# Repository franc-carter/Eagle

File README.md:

# Eagle
Random Collection of my Eagle Design Files

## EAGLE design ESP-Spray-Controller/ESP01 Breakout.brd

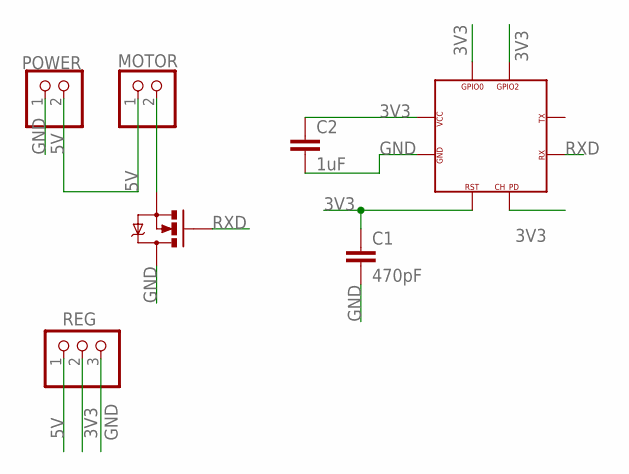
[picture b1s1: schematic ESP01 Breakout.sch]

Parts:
C1: 470pF; CAP-PTH-SMALLEZ
C2: 1uF; CAP-PTH-SMALLEZ
MOTOR: PINHD-1X2/90; 1X02/90
POWER: PINHD-1X2/90; 1X02/90
Q1: MOSFET-NCHANNEL2N7000; TO-92
REG: PINHD-1X3; 1X03
U$2: ESP-01

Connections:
3V3: C1.1, C2.1, REG.2, U$2.CH_PD (CP_PD), U$2.GPIO0, U$2.GPIO2, U$2.RST, U$2.VCC
5V: MOTOR.1, POWER.2, REG.1
GND: C1.2, C2.2, POWER.1, Q1.3 (D), REG.3, U$2.GND
unnamed: MOTOR.2, Q1.1 (S)
RXD: Q1.2 (G), U$2.RXD (RX)

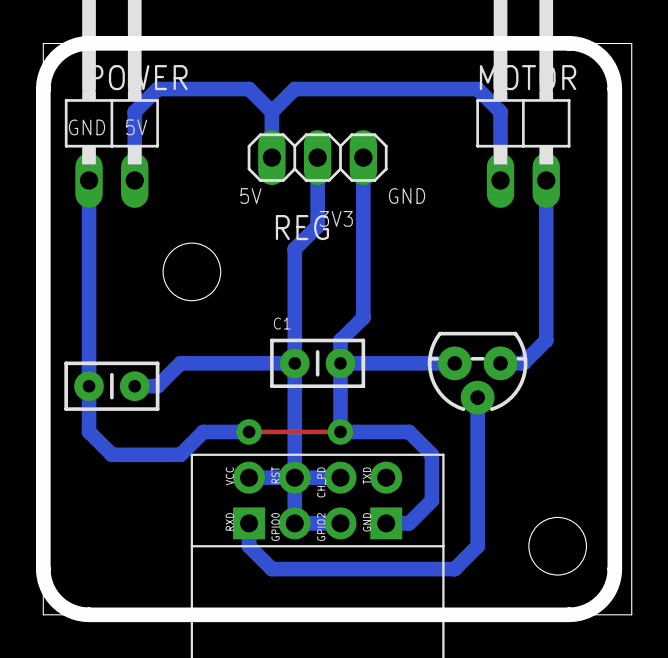
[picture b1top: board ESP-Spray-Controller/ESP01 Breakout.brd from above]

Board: 2 copper layers, 32.3 x 31.7 mm, 7 parts (0 on the bottom side), 5 nets.

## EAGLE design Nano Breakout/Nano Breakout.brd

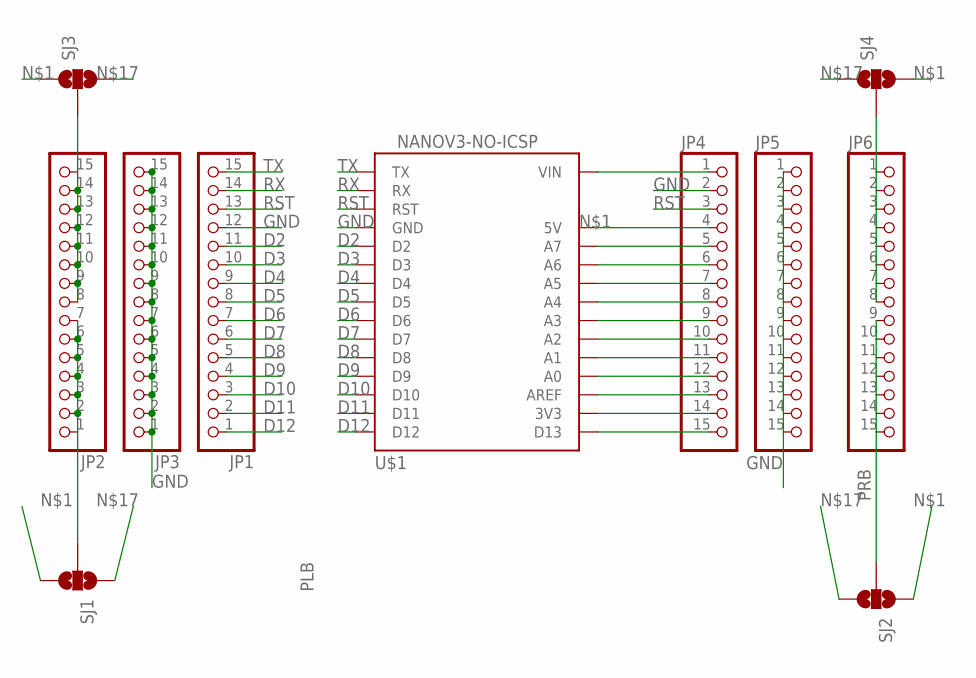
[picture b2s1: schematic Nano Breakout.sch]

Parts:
JP1, JP2, JP3, JP4, JP5, JP6: PINHD-1X15; 1X15
SJ1, SJ2, SJ3, SJ4: JUMPER-PAD-3-NOFULL_BOX_SILK; PAD-JUMPER-3-NO_YES_SILK_FULL_BOX
U$1: NANOV3-NO-ICSP

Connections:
D2: JP1.11, U$1.D2
D3: JP1.10, U$1.D3
D4: JP1.9, U$1.D4
D5: JP1.8, U$1.D5
D6: JP1.7, U$1.D6
D7: JP1.6, U$1.D7
D8: JP1.5, U$1.D8
D9: JP1.4, U$1.D9
D10: JP1.3, U$1.D10
D11: JP1.2, U$1.D11
D12: JP1.1, U$1.D12
GND: JP1.12, JP3.1, JP3.2, JP3.3, JP3.4, JP3.5, JP3.6, JP3.7, JP3.8, JP3.9, JP3.10, JP3.11, JP3.12, JP3.13, JP3.14, JP3.15, JP4.2, JP5.1, JP5.2, JP5.3, JP5.4, JP5.5, JP5.6, JP5.7, JP5.8, JP5.9, JP5.10, JP5.11, JP5.12, JP5.13, JP5.14, JP5.15, U$1.GND@1 (GND), U$1.GND@2 (GND)
unnamed: JP4.4, SJ1.3, SJ2.1, SJ3.1, SJ4.3, U$1.5V
unnamed: JP2.8, JP2.9, JP2.10, JP2.11, JP2.12, JP2.13, JP2.14, JP2.15, SJ3.2
unnamed: JP4.15, U$1.D13
unnamed: JP6.1, JP6.2, JP6.3, JP6.4, JP6.5, JP6.6, JP6.7, JP6.8, SJ4.2
unnamed: JP4.13, U$1.AREF
unnamed: JP4.12, U$1.A0
unnamed: JP4.11, U$1.A1
unnamed: JP4.10, U$1.A2
unnamed: JP4.9, U$1.A3
unnamed: JP4.8, U$1.A4
unnamed: JP4.7, U$1.A5
unnamed: JP4.6, U$1.A6
unnamed: JP4.5, U$1.A7
unnamed: JP4.1, U$1.VIN
unnamed: JP4.14, SJ1.1, SJ2.3, SJ3.3, SJ4.1, U$1.3V3
PLB: JP2.1, JP2.2, JP2.3, JP2.4, JP2.5, JP2.6, JP2.7, SJ1.2
PRB: JP6.9, JP6.10, JP6.11, JP6.12, JP6.13, JP6.14, JP6.15, SJ2.2
RST: JP1.13, JP4.3, U$1.RST1 (RST), U$1.RST2 (RST)
RX: JP1.14, U$1.RX
TX: JP1.15, U$1.TX

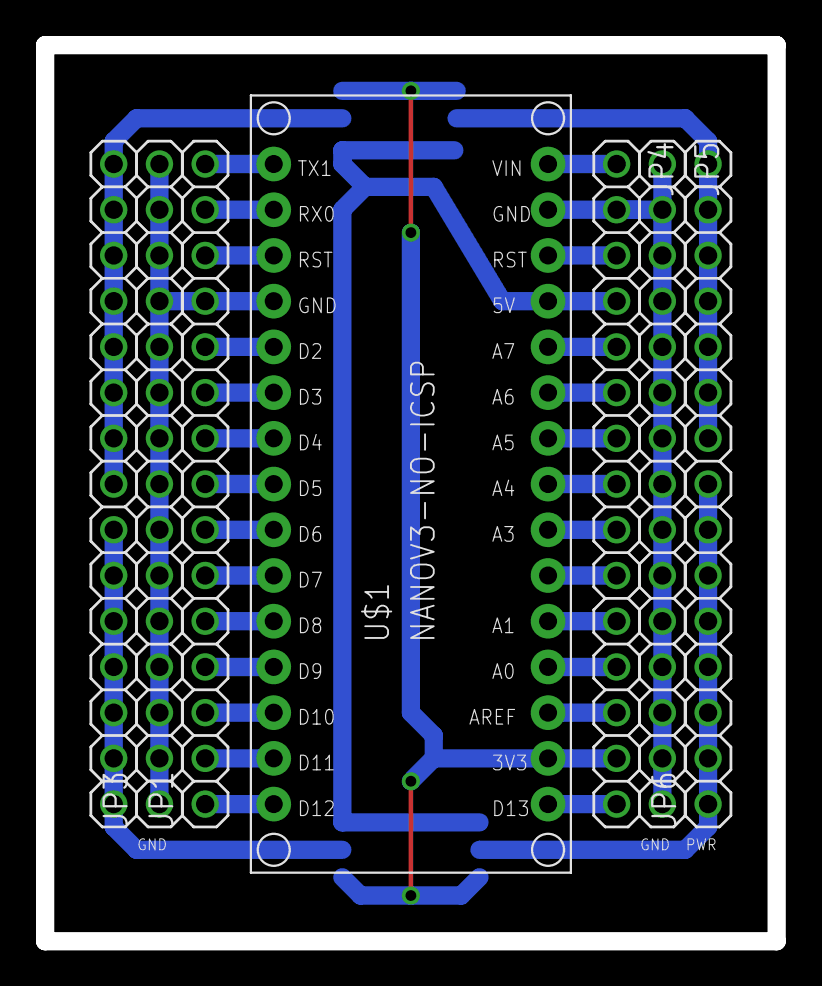
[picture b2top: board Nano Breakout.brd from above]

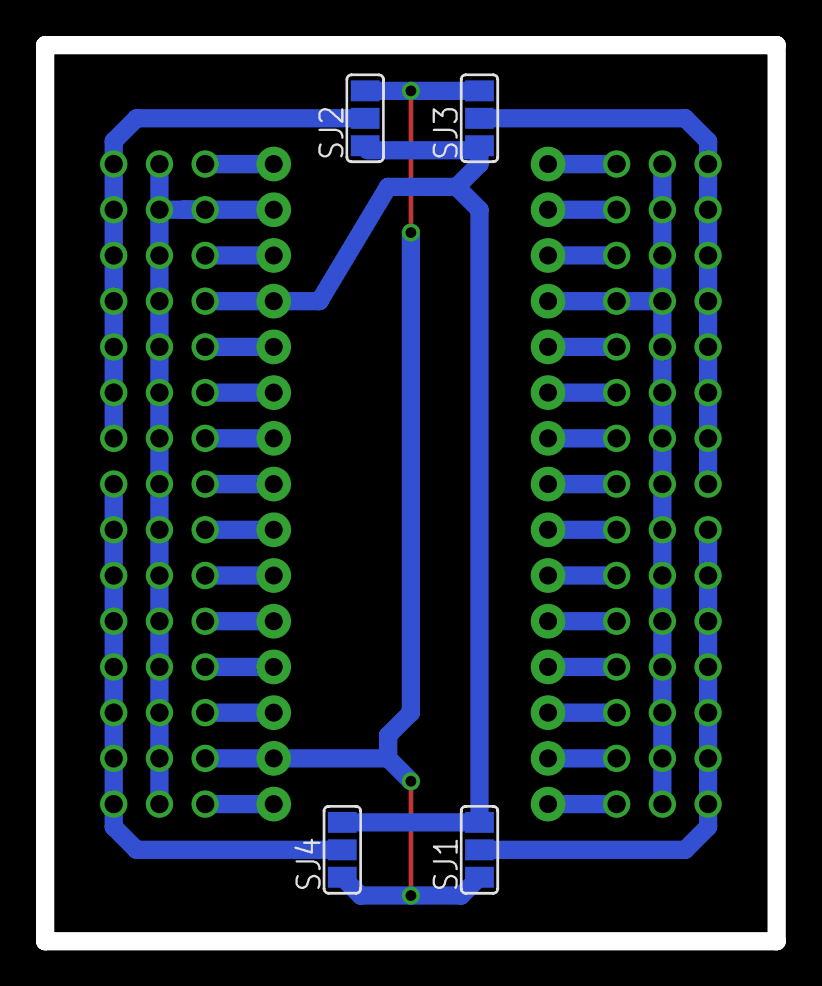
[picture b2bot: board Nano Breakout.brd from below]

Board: 2 copper layers, 40.6 x 49.8 mm, 11 parts (4 on the bottom side), 32 nets.

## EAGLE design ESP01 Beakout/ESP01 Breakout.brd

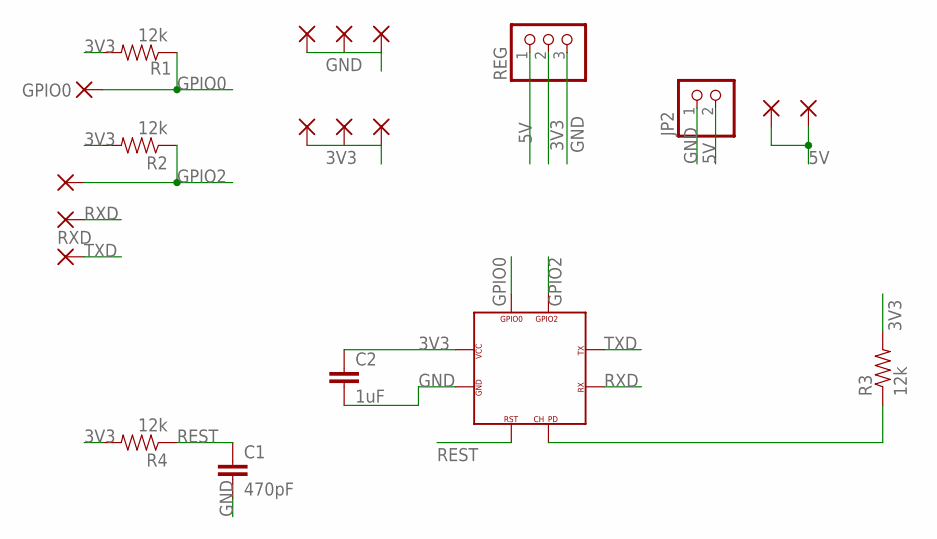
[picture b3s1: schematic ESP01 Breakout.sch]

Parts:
C1: 470pF; CAP-PTH-SMALLEZ
C2: 1uF; CAP-PTH-SMALLEZ
GPIO0, GPIO1, GPIO2, GPIO3, GPIO4, GPIO5, GPIO6, GPIO7, GPIO8, GPIO9, GPIO10: 1,6/0,9
JP2: PINHD-1X2/90; 1X02/90
R1, R2, R3, R4: 12k; AXIAL-0.4
REG: PINHD-1X3; 1X03
RXD: RXD; 1,6/0,9
U$2: ESP-01

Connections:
3V3: C2.1, GPIO6.1, GPIO7.1, GPIO8.1, R1.P$2 (2), R2.P$2 (2), R3.P$2 (2), R4.P$2 (2), REG.2, U$2.VCC
5V: GPIO9.1, GPIO10.1, JP2.2, REG.1
GND: C1.2, C2.2, GPIO1.1, GPIO4.1, GPIO5.1, JP2.1, REG.3, U$2.GND
GPIO0: GPIO0.1, R1.P$1 (1), U$2.GPIO0
GPIO2: GPIO2.1, R2.P$1 (1), U$2.GPIO2
unnamed: R3.P$1 (1), U$2.CH_PD (CP_PD)
REST: C1.1, R4.P$1 (1), U$2.RST
RXD: RXD.1, U$2.RXD (RX)
TXD: GPIO3.1, U$2.TXD (TX)

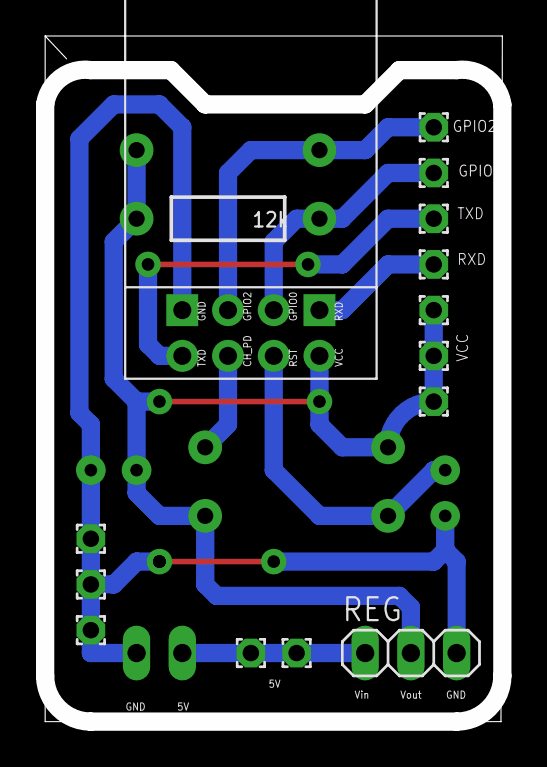
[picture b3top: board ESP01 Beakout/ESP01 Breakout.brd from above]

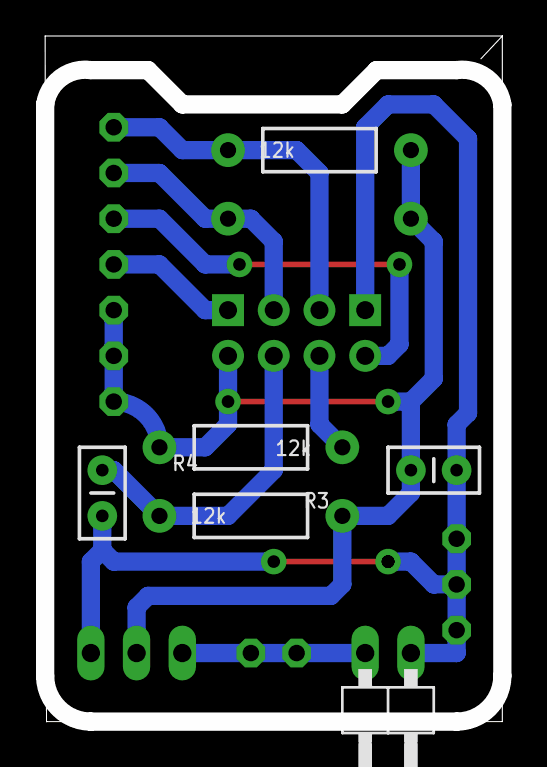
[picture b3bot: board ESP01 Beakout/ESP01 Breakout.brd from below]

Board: 2 copper layers, 25.4 x 37.6 mm, 21 parts (6 on the bottom side), 9 nets.

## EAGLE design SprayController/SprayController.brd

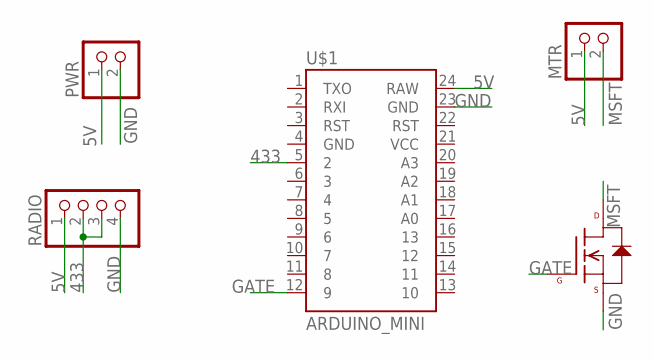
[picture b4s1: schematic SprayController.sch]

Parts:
MTR: PINHD-1X2/90; 1X02/90
PWR: PINHD-1X2/90; 1X02/90
Q1: N-CHANNEL-MOSFET-BSS138; SOT23-3
RADIO: PINHD-1X4/90; 1X04/90
U$1: ARDUINO_MINI

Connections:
5V: MTR.1, PWR.1, RADIO.1, U$1.24 (RAW)
433: RADIO.2, RADIO.3, U$1.5 (2)
GATE: Q1.1 (G), U$1.12 (9)
GND: PWR.2, Q1.2 (S), RADIO.4, U$1.23 (GND)
MSFT: MTR.2, Q1.3 (D)

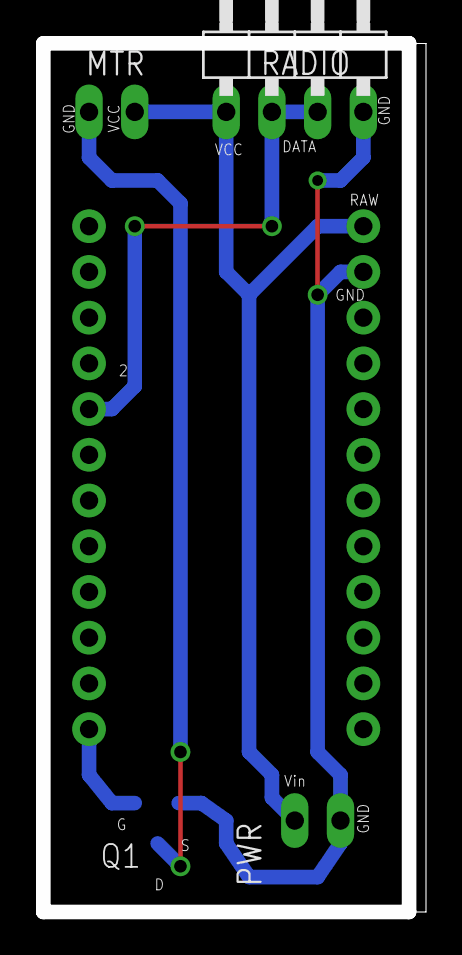
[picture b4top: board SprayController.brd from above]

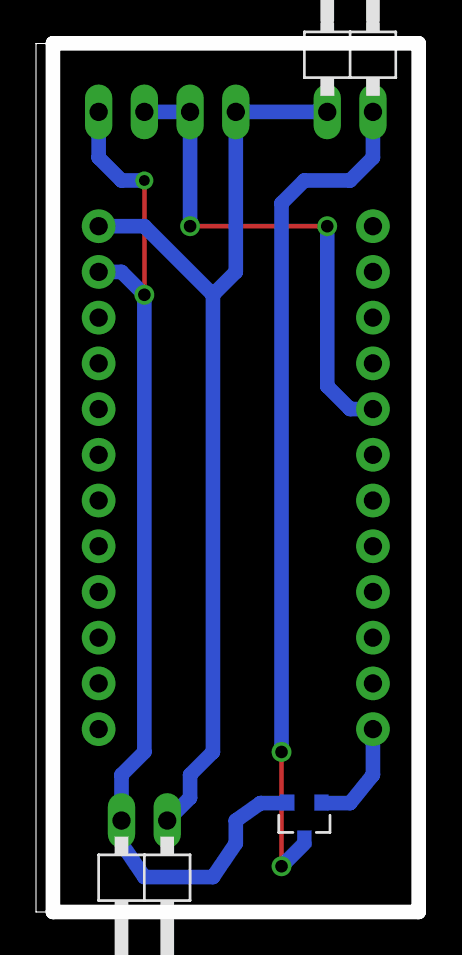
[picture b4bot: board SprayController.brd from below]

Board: 2 copper layers, 20.9 x 48.3 mm, 5 parts (3 on the bottom side), 5 nets.

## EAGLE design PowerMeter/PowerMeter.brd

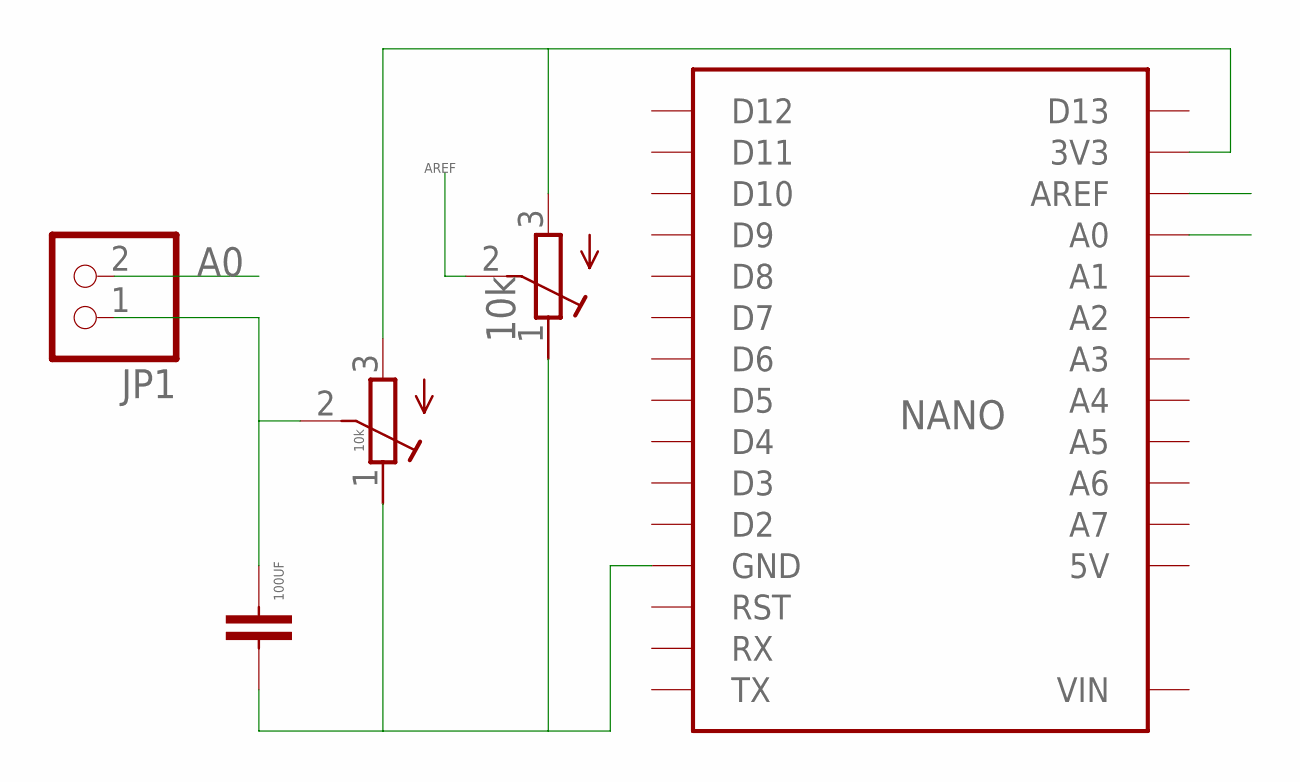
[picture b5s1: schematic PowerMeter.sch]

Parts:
100UF: CAPEZ; CAP-PTH-SMALLEZ
JP1: PINHD-1X2/90; 1X02/90
NANO: NANOV3-NO-ICSP
R1, R3: 10k; RTRIMT93YA

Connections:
3V3: NANO.3V3, R1.3 (E), R3.3 (E)
A0: JP1.2, NANO.A0
AREF: NANO.AREF, R1.2 (S)
GND: 100UF.2, NANO.GND@1 (GND), NANO.GND@2 (GND), R1.1 (A), R3.1 (A)
unnamed: 100UF.1, JP1.1, R3.2 (S)
VIN: NANO.VIN

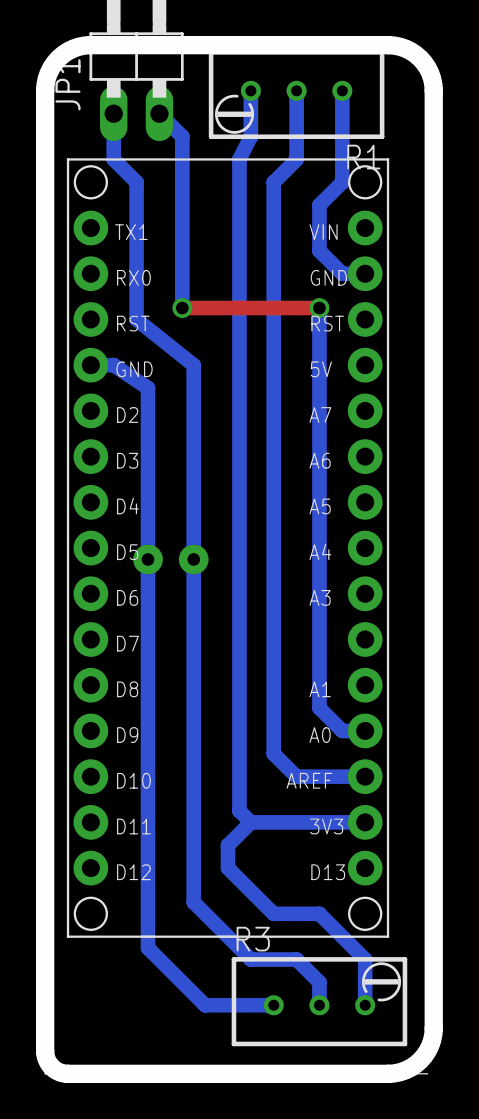
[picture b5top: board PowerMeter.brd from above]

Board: 2 copper layers, 21.6 x 57.1 mm, 5 parts (1 on the bottom side), 5 nets.

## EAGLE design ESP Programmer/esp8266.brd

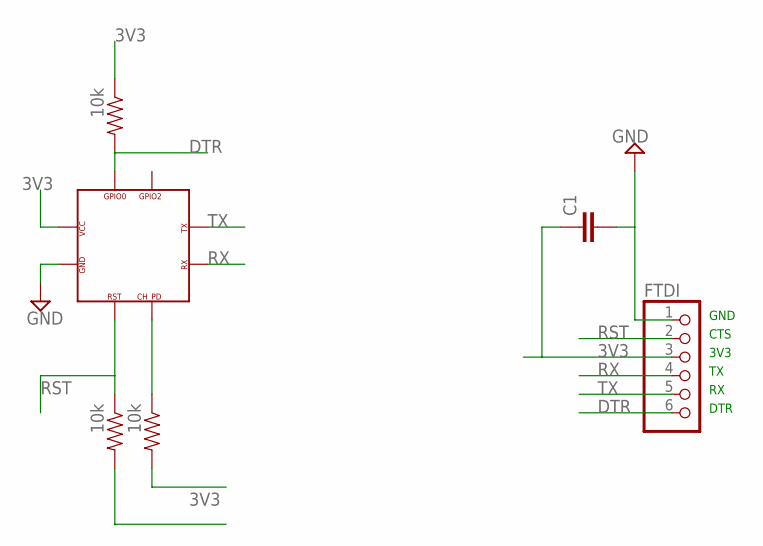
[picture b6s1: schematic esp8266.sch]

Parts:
C1: CAPEZ; CAP-PTH-SMALLEZ
FTDI: PINHD-1X6/90; 1X06/90
R1, R2, R3: 10k; AXIAL-0.5
U$1: ESP-01

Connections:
3V3: C1.1, FTDI.3, R1.P$1 (1), R2.P$2 (2), R3.P$2 (2), U$1.VCC
DTR: FTDI.6, R1.P$2 (2), U$1.GPIO0
GND: C1.2, FTDI.1, U$1.GND
unnamed: R2.P$1 (1), U$1.CH_PD (CP_PD)
RST: FTDI.2, R3.P$1 (1), U$1.RST
RX: FTDI.4, U$1.RXD (RX)
TX: FTDI.5, U$1.TXD (TX)

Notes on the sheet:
GND
CTS
3V3
DTR

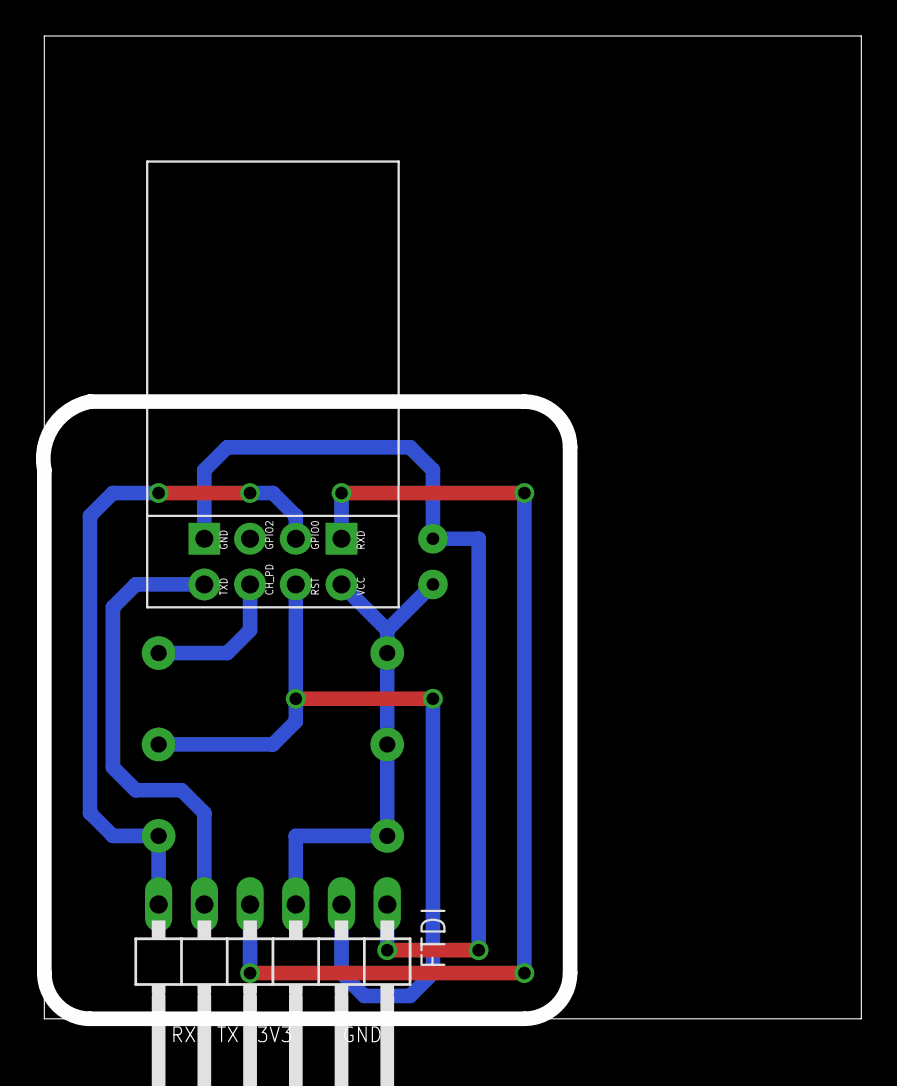
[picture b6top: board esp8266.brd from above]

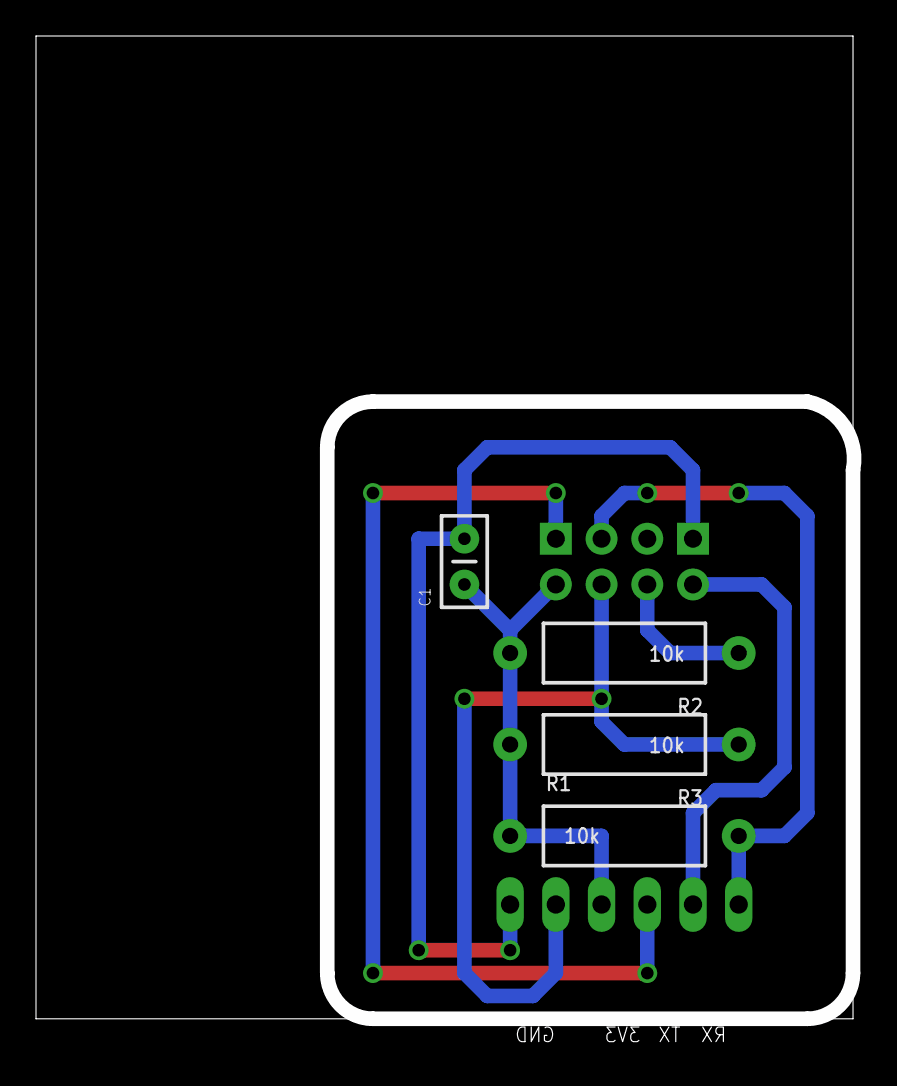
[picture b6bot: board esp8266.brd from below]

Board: 2 copper layers, 45.0 x 55.5 mm, 6 parts (4 on the bottom side), 7 nets.

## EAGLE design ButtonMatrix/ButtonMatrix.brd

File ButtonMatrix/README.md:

Arduino 3 wire matrix keypad

A simple board for the circuit descibred at http://www.instructables.com/id/Arduino-3-wire-Matrix-Keypad/

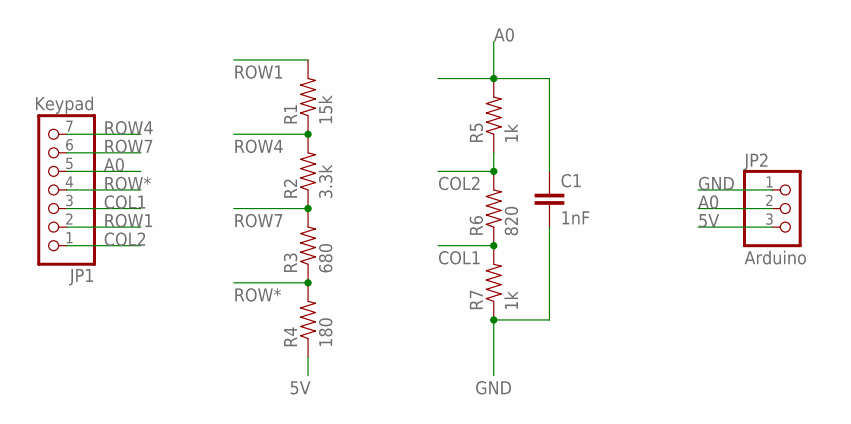
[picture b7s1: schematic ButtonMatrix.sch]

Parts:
C1: 1nF; CAP-PTH-SMALL
JP1: Keypad; 1X07
JP2: Arduino; 1X03
R1: 15k; AXIAL-0.5
R2: 3.3k; AXIAL-0.5
R3: 680; AXIAL-0.5
R4: 180; AXIAL-0.5
R5, R7: 1k; AXIAL-0.5
R6: 820; AXIAL-0.5

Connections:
5V: JP2.3, R4.P$1 (1)
A0: C1.1, JP1.5, JP2.2, R5.P$2 (2)
COL1: JP1.3, R6.P$1 (1), R7.P$2 (2)
COL2: JP1.1, R5.P$1 (1), R6.P$2 (2)
GND: C1.2, JP2.1, R7.P$1 (1)
ROW1: JP1.2, R1.P$2 (2)
ROW4: JP1.7, R1.P$1 (1), R2.P$2 (2)
ROW7: JP1.6, R2.P$1 (1), R3.P$2 (2)
ROW*: JP1.4, R3.P$1 (1), R4.P$2 (2)

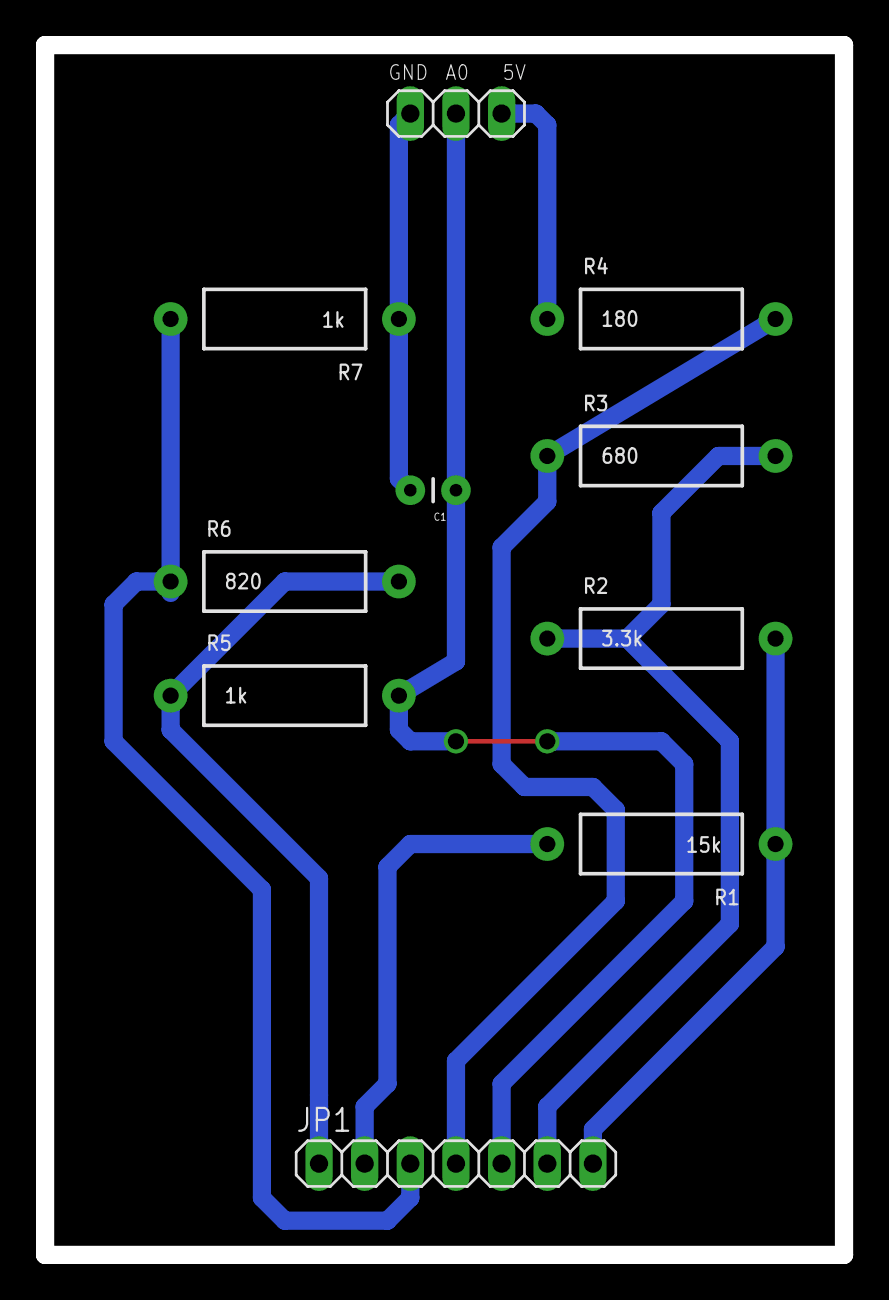
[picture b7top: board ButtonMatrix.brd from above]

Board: 2 copper layers, 44.5 x 67.3 mm, 10 parts (0 on the bottom side), 9 nets.

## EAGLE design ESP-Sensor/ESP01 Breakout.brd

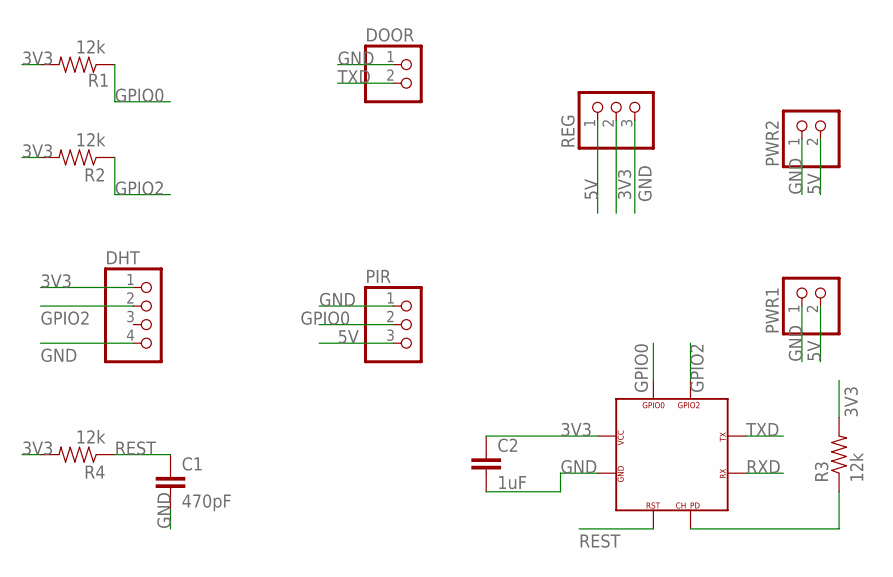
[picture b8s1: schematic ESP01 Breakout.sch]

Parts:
C1: 470pF; CAP-PTH-SMALLEZ
C2: 1uF; CAP-PTH-SMALLEZ
DHT: PINHD-1X4; 1X04
DOOR: PINHD-1X2/90; 1X02/90
PIR: PINHD-1X3; 1X03
PWR1, PWR2: PINHD-1X2/90; 1X02/90
R1, R2, R3, R4: 12k; AXIAL-0.4
REG: PINHD-1X3; 1X03
U$2: ESP-01

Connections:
3V3: C2.1, DHT.1, R1.P$2 (2), R2.P$2 (2), R3.P$2 (2), R4.P$2 (2), REG.2, U$2.VCC
5V: PIR.3, PWR1.2, PWR2.2, REG.1
GND: C1.2, C2.2, DHT.4, DOOR.1, PIR.1, PWR1.1, PWR2.1, REG.3, U$2.GND
GPIO0: PIR.2, R1.P$1 (1), U$2.GPIO0
GPIO2: DHT.2, R2.P$1 (1), U$2.GPIO2
unnamed: R3.P$1 (1), U$2.CH_PD (CP_PD)
REST: C1.1, R4.P$1 (1), U$2.RST
RXD: U$2.RXD (RX)
TXD: DOOR.2, U$2.TXD (TX)

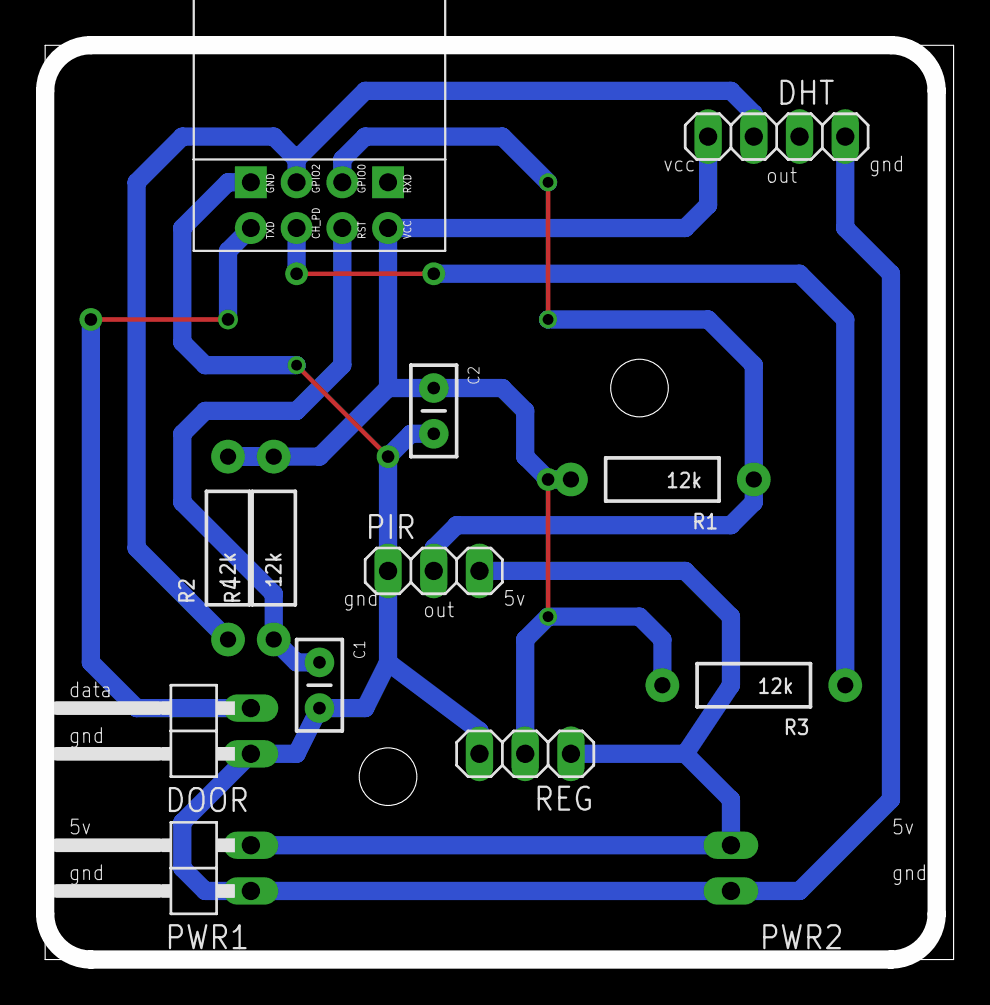
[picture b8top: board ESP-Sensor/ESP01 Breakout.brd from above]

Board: 2 copper layers, 50.0 x 50.8 mm, 13 parts (1 on the bottom side), 8 nets.

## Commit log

2015-05-06 readme for the button matrix
2015-05-06 removed old 'Power' directory
2015-05-06 readme for the rgb strip
2015-05-06 more readmes
2015-05-07 clean up Blinds Stepper
2015-05-07 blinds stepper update
2015-06-28 remove old dead projects, add esp-01 sensor stuff
2015-07-15 many changes

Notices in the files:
parts and their libraries:
SparkFun-Passives: Licensing: Creative Commons ShareAlike 4.0 International - https://creativecommons.org/licenses/by-sa/4.0
